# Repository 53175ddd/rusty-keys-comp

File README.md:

# rusty-keys-comp
RustyKeys の互換品｜AE-RP2040 対応版

派生元：<https://github.com/KOBA789/rusty-keys>

詳しくは派生元リポジトリをご覧ください

# 主な変更点

- マイコンボードを AE-RP2040 に変更
- ソケット方式に変更
  - キースイッチの交換が可能に

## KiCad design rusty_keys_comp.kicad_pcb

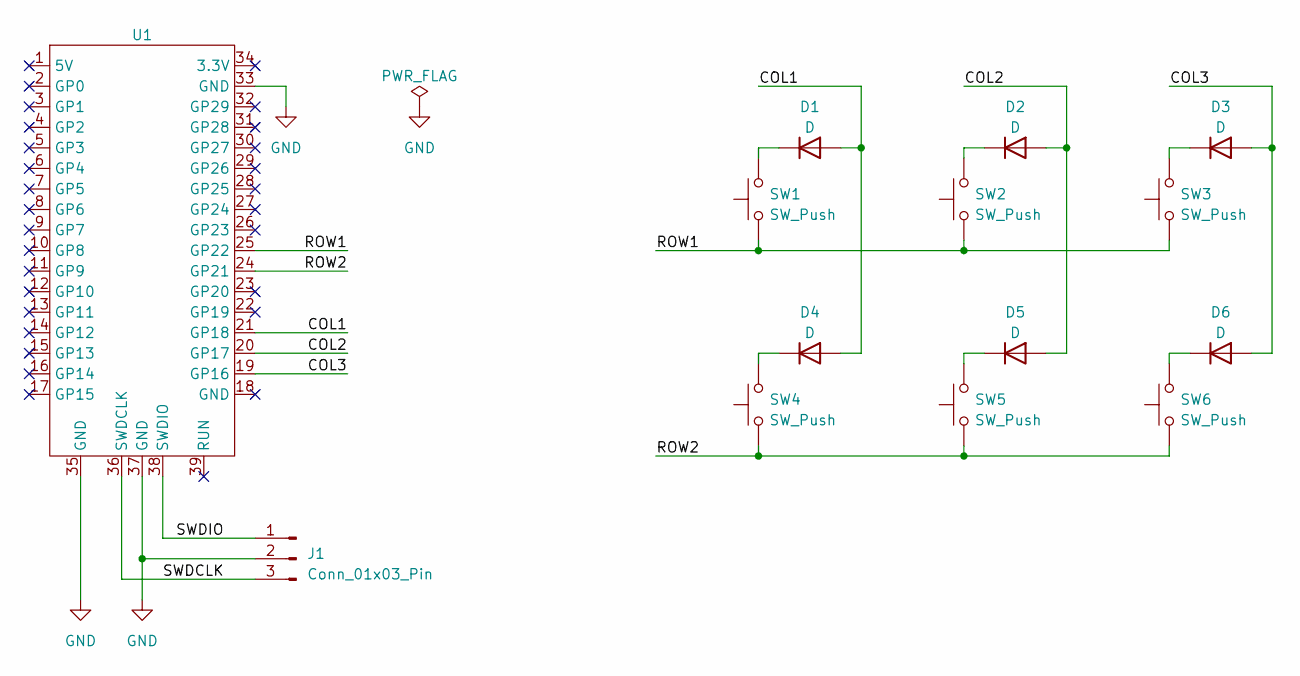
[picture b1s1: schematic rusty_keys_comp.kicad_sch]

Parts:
D1, D2, D3, D4, D5, D6: D; D_A-405_P10.16mm_Horizontal
J1: Conn_01x03_Pin; PinHeader_1x03_P2.54mm_Horizontal
SW1, SW2, SW3, SW4, SW5, SW6: SW_Push; SW_Cherry_MX_1.00u_Socket
U1: AE-RP2040

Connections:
/COL1: D1.2 (A), D4.2 (A), U1.21 (GP18)
/COL2: D2.2 (A), D5.2 (A), U1.20 (GP17)
/COL3: D3.2 (A), D6.2 (A), U1.19 (GP16)
/ROW1: SW1.1, SW2.1, SW3.1, U1.25 (GP22)
/ROW2: SW4.1, SW5.1, SW6.1, U1.24 (GP21)
/SWDCLK: J1.3, U1.36 (SWDCLK)
/SWDIO: J1.1, U1.38 (SWDIO)
GND: J1.2, U1.33 (GND), U1.35 (GND), U1.37 (GND)
unnamed: D1.1 (K), SW1.2
unnamed: D2.1 (K), SW2.2
unnamed: D3.1 (K), SW3.2
unnamed: D4.1 (K), SW4.2
unnamed: D5.1 (K), SW5.2
unnamed: D6.1 (K), SW6.2

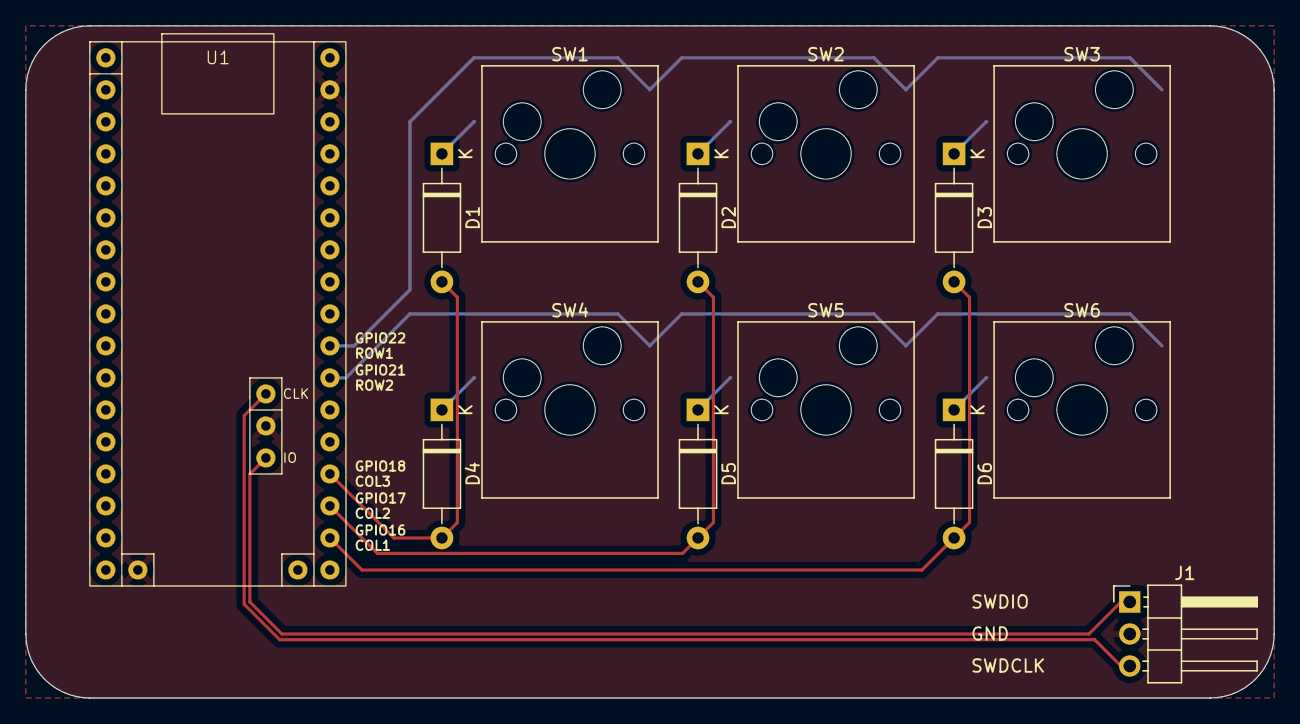
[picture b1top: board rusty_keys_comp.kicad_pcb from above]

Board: 2 copper layers, 99.1 x 53.3 mm, 14 parts (0 on the bottom side), 14 nets.

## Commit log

2024-06-19 ロゴ削除
